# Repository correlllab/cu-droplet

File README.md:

497-6781-1-ND

Droplets: A Swarm Robotics Platform
==========

[Click here to get started!](https://github.com/correlllab/cu-droplet/blob/master/getting_started.md)

The platform has been produced by the Correll Robotics Lab at the University of Colorado Boulder. It is envisioned to be a scalable robotics experimentation environment.

The hardware is comprised of actual robots, and the test bed/floor that experiments are run on. The robots are capable of sensing IR and RGB intensities, actuation using vibration motors, and IR communication. The embedded software layer is what we use to write and compile on-board code for the droplets. Each robot is equipped with an Atmel xmega-128a3u microprocessor capable of running embedded-c.

A simulator has also been developed for this platform. This code has its own repo on <a href="https://github.com/correlllab/cu-droplet-sim">github</a>.

This work is available under a <a href="https://creativecommons.org/licenses/by-nc-sa/4.0/" >Creative Commons Attribution-NonCommercial-ShareAlike License. </a>

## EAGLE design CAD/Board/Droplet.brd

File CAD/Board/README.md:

# README

The files included in this folder are Droplet board schematic files to be used with the EAGLE design program.

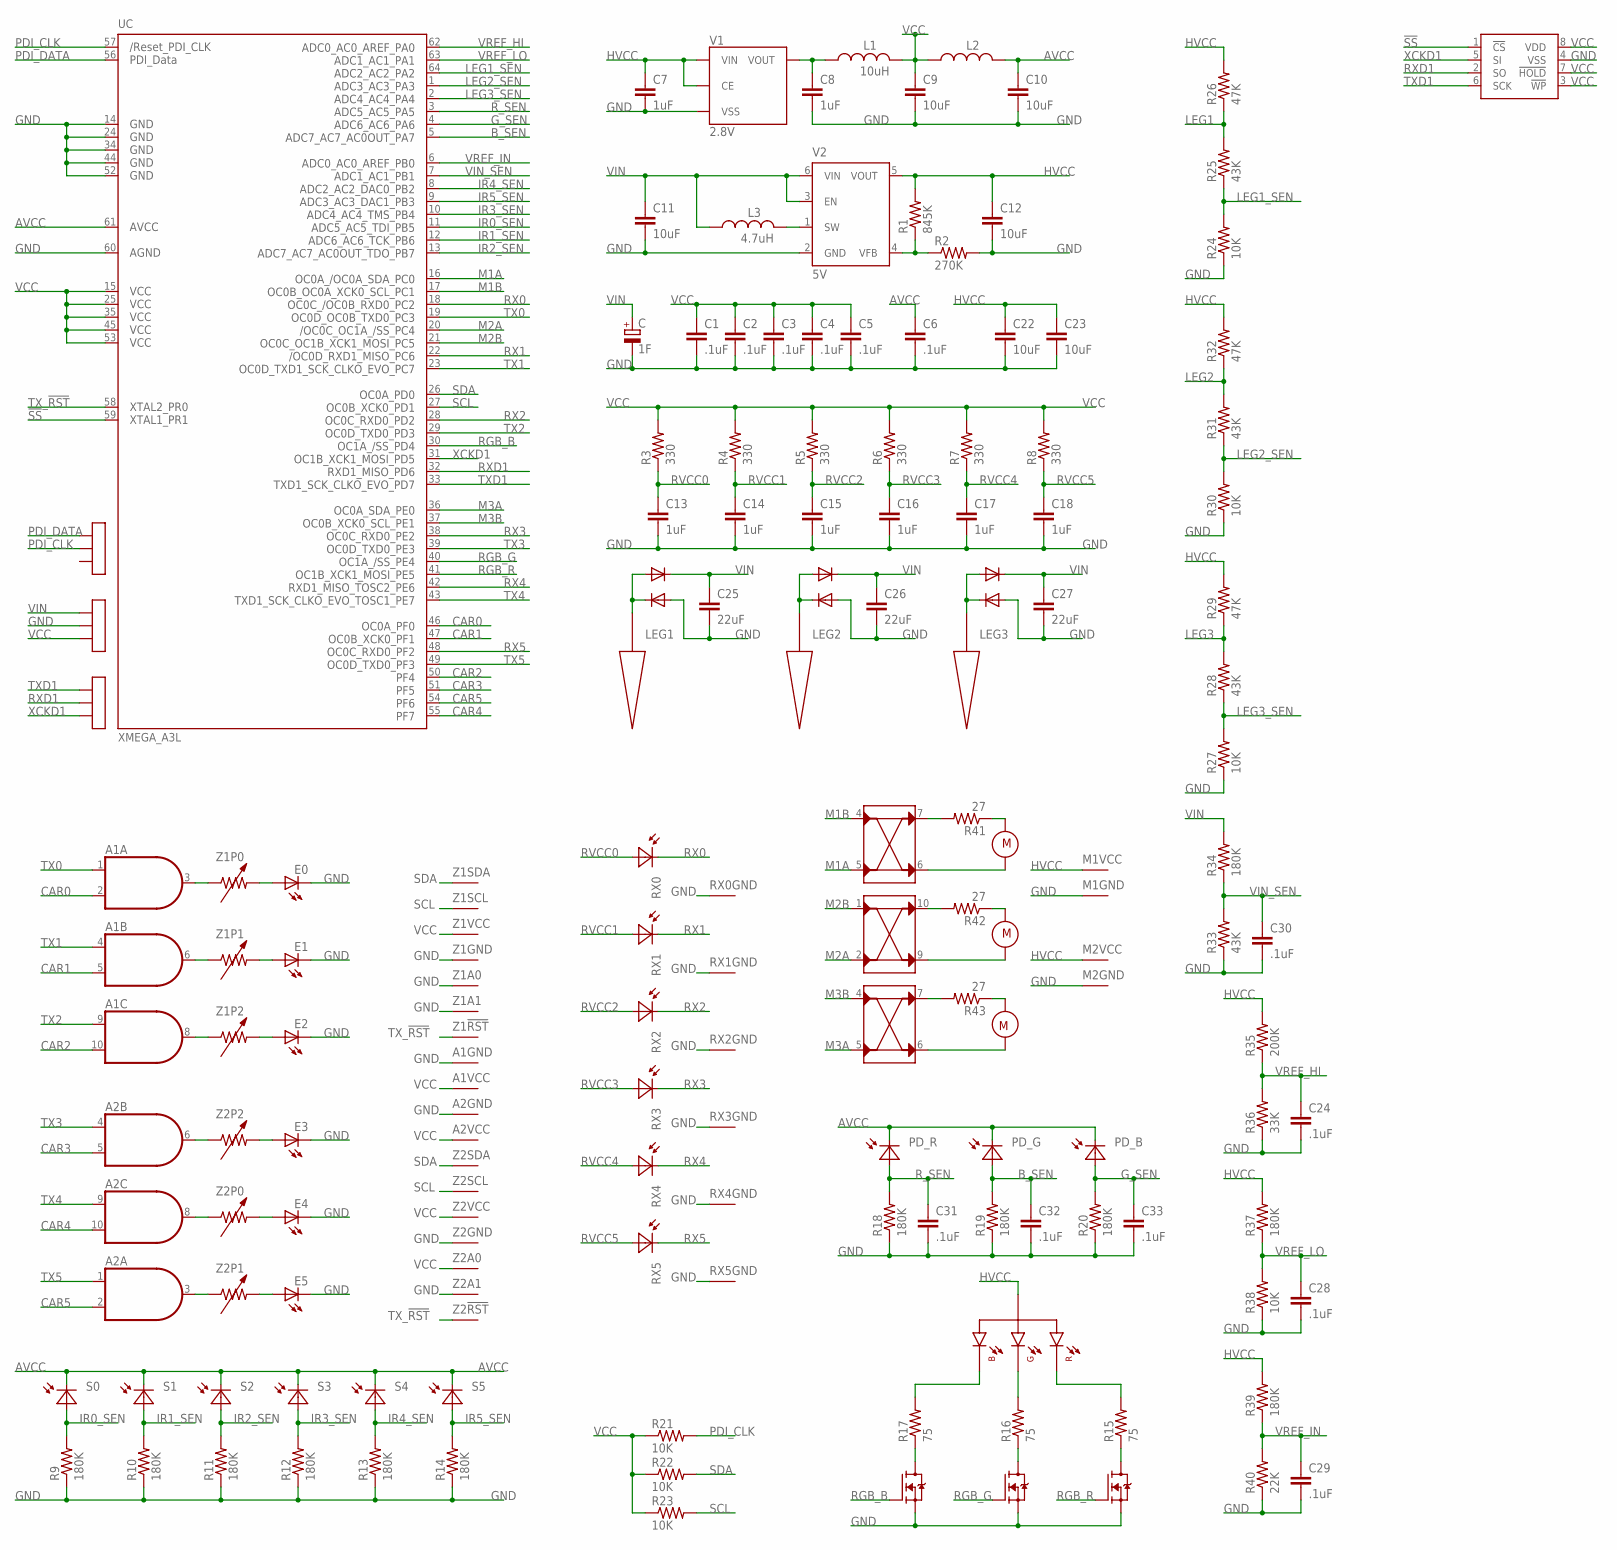
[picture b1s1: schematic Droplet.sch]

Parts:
A1: 7408_X4"; DHVQFN14-L; DIGIKEY 568-2993-1-ND
A2: 7408_X4"; DHVQFN14-L
C: 1F; SUPERCAP
C1, C2, C3, C4, C5, C6, C24, C28, C29, C30, C31, C32, C33: .1uF; 0402
C7, C8, C13, C14, C15, C16, C17, C18: 1uF; 0402
C9, C10, C11, C12, C22, C23: 10uF; 0603
C25, C26, C27: 22uF; 0805
D1, D2, D3, D4, D5, D6: DIODE; SOD-123
E0, E1, E2, E3, E4, E5: IR_LED; 1208-IR
F1, F2: MOSFET-N_X2; SOT-363
L1: 10uH; 0805
L2: INDUCTOR0603; 0603
L3: 4.7uH; 1210
LED: RGB_LED
LEG1, LEG2, LEG3: LEG
M1, M2: HALF-MOTOR_CONTROLLER; DFN-10-EJ
MEM: MRAM; DFN-8
MOT1, MOT2, MOT3: MOTOR; MOTOR_PADS
P1, P2, P3: EDGE_PORT_3; EDGE_CONNECTOR3
PD_B: RGB_PHOTODIODE; RGB_SENSOR
PD_G: RGB_PHOTODIODE; RGB_SENSOR
PD_R: RGB_PHOTODIODE; RGB_SENSOR
R1: 845K; 0402
R2: 270K; 0402
R3, R4, R5, R6, R7, R8: 330; 0402
R9, R10, R11, R12, R13, R14, R18, R19, R20, R34, R37, R39: 180K; 0402
R15, R16, R17: 75; 0402
R21, R22, R23, R24, R27, R30, R38: 10K; 0402
R25, R28, R31, R33: 43K; 0402
R26, R29, R32: 47K; 0402
R35: 200K; 0402
R36: 33K; 0402
R40: 22K; 0402
R41, R42, R43: 27; 0402
RX0, RX1, RX2, RX3, RX4, RX5: IR_RECEIVER
S0, S1, S2, S3, S4, S5: IR_PHOTODIODE; 1208-IR
UC: XMEGA_A3L; MLF-64-L
V1: 2.8V; SOT-25
V2: 5V; SOT-23-6
Z1, Z2: VAR_RESISTOR_X4; QFN-20

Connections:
!SS: MEM.1 (!CS), UC.59 (PR1)
AVCC: C6.1, C10.1, L2.2, PD_B.C1 (C), PD_B.C2 (C), PD_G.C1 (C), PD_G.C2 (C), PD_R.C1 (C), PD_R.C2 (C), S0.C, S1.C, S2.C, S3.C, S4.C, S5.C, UC.61 (AVCC)
B_SEN: C32.1, PD_G.A1 (A), PD_G.A2 (A), R19.2, UC.5 (PA7)
CAR0: A1.2 (I1), UC.46 (PF0)
CAR1: A1.5 (I1), UC.47 (PF1)
CAR2: A1.10 (I1), UC.50 (PF4)
CAR3: A2.5 (I1), UC.51 (PF5)
CAR4: A2.10 (I1), UC.55 (PF7)
CAR5: A2.2 (I1), UC.54 (PF6)
GND: A1.7 (1), A2.7 (1), C.N (-), C1.2, C2.2, C3.2, C4.2, C5.2, C6.2, C7.2, C8.2, C9.2, C10.2, C11.2, C12.2, C13.2, C14.2, C15.2, C16.2, C17.2, C18.2, C22.2, C23.2, C24.2, C25.2, C26.2, C27.2, C28.2, C29.2, C30.2, C31.2, C32.2, C33.2, D2.A, D4.A, D6.A, E0.C, E1.C, E2.C, E3.C, E4.C, E5.C, F1.1 (S), F1.4 (S), F2.1 (S), M1.3 (1), M2.3 (1), MEM.4 (VSS), P2.2A (2), P2.2B (2), R2.2, R9.1, R10.1, R11.1, R12.1, R13.1, R14.1, R18.1, R19.1, R20.1, R24.1, R27.1, R30.1, R33.1, R36.1, R38.1, R40.1, RX0.3 (1), RX1.3 (1), RX2.3 (1), RX3.3 (1), RX4.3 (1), RX5.3 (1), UC.14 (GND1), UC.24 (GND2), UC.34 (GND3), UC.44 (GND4), UC.52 (GND5), UC.60 (AGND), V1.VSS, V2.2 (GND), Z1.2 (1), Z1.5 (1), Z1.14 (1), Z2.5 (1), Z2.14 (1)
G_SEN: C33.1, PD_B.A1 (A), PD_B.A2 (A), R20.2, UC.4 (PA6)
HVCC: C7.1, C12.1, C22.1, C23.1, LED.2 (ANODE), M1.8 (1), M2.8 (1), R1.2, R26.2, R29.2, R32.2, R35.2, R37.2, R39.2, V1.CE, V1.VIN, V2.5 (VOUT)
IR0_SEN: R9.2, S0.A, UC.11 (PB5)
IR1_SEN: R10.2, S1.A, UC.12 (PB6)
IR2_SEN: R11.2, S2.A, UC.13 (PB7)
IR3_SEN: R12.2, S3.A, UC.10 (PB4)
IR4_SEN: R13.2, S4.A, UC.8 (PB2)
IR5_SEN: R14.2, S5.A, UC.9 (PB3)
LEG1: D1.A, D2.C, LEG1.1, R25.2, R26.1
LEG1_SEN: R24.2, R25.1, UC.64 (PA2)
LEG2: D3.A, D4.C, LEG2.1, R31.2, R32.1
LEG2_SEN: R30.2, R31.1, UC.1 (PA3)
LEG3: D5.A, D6.C, LEG3.1, R28.2, R29.1
LEG3_SEN: R27.2, R28.1, UC.2 (PA4)
M1A: M1.5 (IN2), UC.16 (PC0)
M1B: M1.4 (IN1), UC.17 (PC1)
M1Z: M1.6 (OUT2), MOT1.2
M2A: M1.2 (IN2), UC.20 (PC4)
M2B: M1.1 (IN1), UC.21 (PC5)
M2Z: M1.9 (OUT2), MOT2.2
M3A: M2.5 (IN2), UC.36 (PE0)
M3B: M2.4 (IN1), UC.37 (PE1)
M3Z: M2.6 (OUT2), MOT3.1
unnamed: C8.1, L1.1, V1.VOUT
unnamed: R1.1, R2.1, V2.4 (VFB)
unnamed: E0.A, Z1.10 (2)
unnamed: E1.A, Z1.7 (2)
unnamed: E2.A, Z1.17 (2)
unnamed: L3.2, V2.1 (SW)
unnamed: E3.A, Z2.17 (2)
unnamed: E4.A, Z2.10 (2)
unnamed: E5.A, Z2.7 (2)
unnamed: A1.3 (O), Z1.9 (1)
unnamed: A1.6 (O), Z1.8 (1)
unnamed: A1.8 (O), Z1.18 (1)
unnamed: A2.6 (O), Z2.18 (1)
unnamed: A2.8 (O), Z2.9 (1)
unnamed: A2.3 (O), Z2.8 (1)
unnamed: F1.6 (D), R17.1
unnamed: F1.3 (D), R16.1
unnamed: F2.6 (D), R15.1
unnamed: LED.3 (B), R17.2
unnamed: LED.4 (G), R16.2
unnamed: M1.7 (OUT1), R41.2
unnamed: MOT1.1, R41.1
unnamed: M1.10 (OUT1), R42.2
unnamed: MOT2.1, R42.1
unnamed: LED.1 (R), R15.2
unnamed: M2.7 (OUT1), R43.2
unnamed: MOT3.2, R43.1
PDI_CLK: P1.2A (2), P1.2B (2), R21.2, UC.57 (RESET)
PDI_DATA: P1.1A (1), P1.1B (1), UC.56 (PDI_DATA)
RGB_B: F1.2 (G), UC.30 (PD4)
RGB_G: F1.5 (G), UC.40 (PE4)
RGB_R: F2.2 (G), UC.41 (PE5)
RVCC0: C13.1, R3.1, RX0.2 (A)
RVCC1: C14.1, R4.1, RX1.2 (A)
RVCC2: C15.1, R5.1, RX2.2 (A)
RVCC3: C16.1, R6.1, RX3.2 (A)
RVCC4: C17.1, R7.1, RX4.2 (A)
RVCC5: C18.1, R8.1, RX5.2 (A)
RX0: RX0.1 (C), UC.18 (PC2)
RX1: RX1.1 (C), UC.22 (PC6)
RX2: RX2.1 (C), UC.28 (PD2)
RX3: RX3.1 (C), UC.38 (PE2)
RX4: RX4.1 (C), UC.42 (PE6)
RX5: RX5.1 (C), UC.48 (PF2)
RXD1: MEM.2 (SO), P3.2A (2), P3.2B (2), UC.32 (PD6)
R_SEN: C31.1, PD_R.A1 (A), PD_R.A2 (A), R18.2, UC.3 (PA5)
SCL: R23.2, UC.27 (PD1), Z1.3 (1), Z2.3 (1)
SDA: R22.2, UC.26 (PD0), Z1.4 (1), Z2.4 (1)
TX0: A1.1 (I0), UC.19 (PC3)
TX1: A1.4 (I0), UC.23 (PC7)
TX2: A1.9 (I0), UC.29 (PD3)
TX3: A2.4 (I0), UC.39 (PE3)
TX4: A2.9 (I0), UC.43 (PE7)
TX5: A2.1 (I0), UC.49 (PF3)
TXD1: MEM.6 (SCK), P3.1A (1), P3.1B (1), UC.33 (PD7)
TX_!RST: UC.58 (PR0), Z1.13 (1), Z2.13 (1)
VCC: A1.14 (1), A2.14 (1), C1.1, C2.1, C3.1, C4.1, C5.1, C9.1, L1.2, L2.1, MEM.3 (!WP), MEM.7 (!HOLD), MEM.8 (VDD), P2.3A (3), P2.3B (3), R3.2, R4.2, R5.2, R6.2, R7.2, R8.2, R21.1, R22.1, R23.1, UC.15 (VCC1), UC.25 (VCC2), UC.35 (VCC3), UC.45 (VCC4), UC.53 (VCC5), Z1.15 (1), Z2.2 (1), Z2.15 (1)
VIN: C.P (+), C11.1, C25.1, C26.1, C27.1, D1.C, D3.C, D5.C, L3.1, P2.1A (1), P2.1B (1), R34.2, V2.3 (EN), V2.6 (VIN)
VIN_SEN: C30.1, R33.2, R34.1, UC.7 (PB1)
VREF_HI: C24.1, R35.1, R36.2, UC.62 (PA0)
VREF_IN: C29.1, R39.1, R40.2, UC.6 (PB0)
VREF_LO: C28.1, R37.1, R38.2, UC.63 (PA1)
XCKD1: MEM.5 (SI), P3.3A (3), P3.3B (3), UC.31 (PD5)

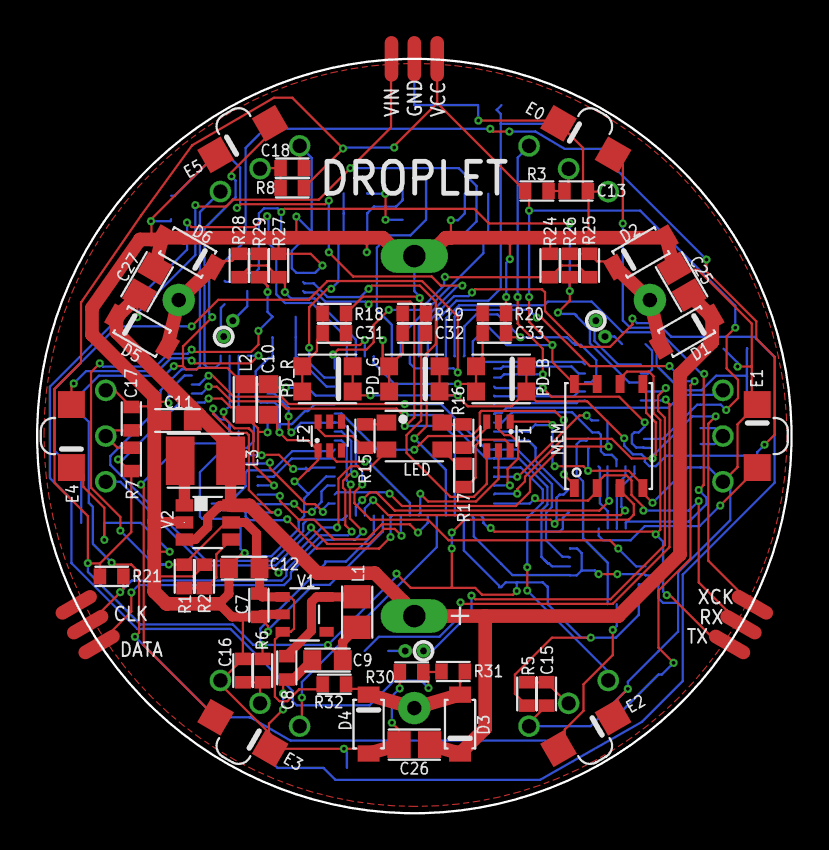
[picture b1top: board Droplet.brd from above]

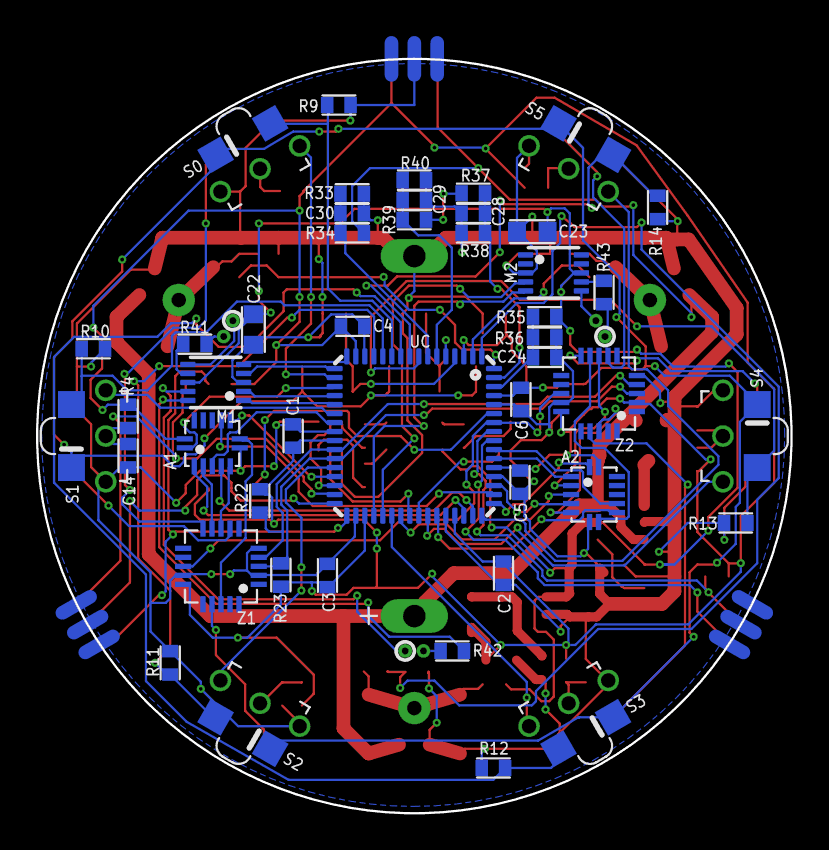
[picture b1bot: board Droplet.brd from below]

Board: 2 copper layers, 41.9 x 41.9 mm, 126 parts (56 on the bottom side), 96 nets.

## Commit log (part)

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2016-07-02 A runnin version of distributed camouflage algorithm
2016-07-03 Modify for the non-audio droplets, and calibrate the rgb sensors. The baselines were reset to 0 which I don't think is right, so I comment those lines.
2016-07-04 Need to modify according the notes
2016-07-06 Add print functions to print information needed afterwards
2016-07-06 Nothing special
2016-07-06 add calibration for RGB with white light
2016-07-07 Modify to add calibreation by wrting the dark readings to EEPROM. By John Klingner
2016-07-07 A working one, don't want to change the logic again.
2016-07-08 V-0.9
2016-07-10 Eulerian Distance for colors seems no better
2016-07-12 small change on pattern descriptors?
2016-07-16 Version with 3 patterns, doesnt work well on the droplet, mainly the pattern fomation phase. I think that might be the wrong reflection setting?
2016-07-19 Updating master with minor updates to things from ping_pong branch. Mostly, these are improvements to the Waiting for TWI error printout.
2016-07-19 Finally added all the files needed to order your own Droplet Circuit Boards
2016-07-19 Recommenting after pulling from master.
2016-08-04 Updated the API document to include additional information about serial commands, printf, and size-explicit variable types.
2016-09-16 Code that was (almost) used for ICRA.
2016-09-22 Made good progress implementing particle filter, though there are a lot of comments so far.
2016-09-29 Particle filter working pretty well for two droplets, though it's slow to converge.
2016-09-29 Changes updated
2016-09-30 Updated range_model for improve RNB performance.
2016-10-11 ..Accidentally did a ton of refactoring. Took all variables and functions which only needed local scope and moved them to the C file and made them static. Also modified the scheduler to go back to ju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
2016-10-12 Major bugs worked out of the batch particle updates. Trouble with batch approach is that trying to do all the computation all at once means the computation takes longer than a frame. About twice as l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
2016-10-13 Made some good progress cleaning things up from yesterday's big changes. Switched to x,y,o difference tracking instead of r,b,h, but kept it so that it's easy to switch from one to the other. x,y,o i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
2016-10-15 Particle filter seems to be working well/correctly for jsut two robots. Some more subtle issues with multiple robots. I think it's now working roughly as well as it did before I lumped everything tog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
2016-10-25 I've weeded out all of the bugs I can with particle filter stuff. If important bugs remain, they're subtle. Overall results are still not great. I'm going to collect all of the data from some droplet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
2016-10-27 This code is for collecting and printing all the data a droplet has to consider for figuring out its position.
2016-10-27 Trying to set things back how they were before I tore out all the particle filter stuff.
2016-10-29 End of week commit. Still working on adding don't-conflict-with-source logic to particle filter.
2016-10-31 Some more changes from my working branch. did some more work on the collisions checking - it now requires pre-calibration.
2016-11-02 Made some good progress on bugs in the camouflage code.
2016-11-05 Yang: adding corner reflection as suggested by John in function changeColor
2016-11-15 Small fixes to user_template.c
2016-11-23 Going away for Thanksgiving commit.
2016-11-30 Master in good shape again.
2016-12-01 Tests working pretty well.
2016-12-02 Added reference PDF for Audio Droplets
2016-12-14 Working.. okay? Worked in small test. Struggling with larger test.
2016-12-16 Few changes needed to be made for compilability.
2016-12-29 Made some improvements to the code; it actually seems to be working fairly well in tests of around a dozen droplets.
2017-01-14 Finished updating with 80% more Kalman approach. Early indications are that it works like magic. Will do full-scale tests, next.
2017-01-19 Full kalman mostly implemented.
2017-01-26 Trying a tweak to how this works.
2017-01-26 Made some forthere tweaks. Going to turn back on the full r,b,h capabilities of range and bearing.
2017-01-30 Need to switch branches.
2017-02-03 Finished re-fixing range and bearing (now with heading reincluded). That, on top of the Covariance Interference algorithm, seems to be working very well indeed. Tentatively best I've seen; still need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
2017-02-08 continued progress! multi-filter implemented with optimal (I think) fusing of the multiple filters.
2017-02-08 Accidentally left one thing in user_template.c, needed to clean it out.
2017-02-08 Moved the pong-specific stuff out of positions.c and in to pong.c
2017-02-14 Further improvements!
2017-02-23 Haven't been able to make much progress due to multiprogrammer failure, but I want to switch branches.
2017-02-28 Added functions to read other droplets' motor_adjust values and
    chec if a droplet is calibrated or not.
2017-03-02 More changes to motor_adjust_values passing
2017-03-05 printing read_motor_settings after storing in an array
2017-03-17 edge following implemented without using range and bearing- works only for close distances
2017-03-21 Updated send_motor_settings
2017-03-22 This didn't get fixed right when moving code to master.
2017-03-22 Fixed the weird little issue.
2017-03-23 Finished stripping out the four-filters-at-once stuff.
2017-04-01 Back down to single filter, but I left all the pieces for multi-filter approach commented out in case I feel the need to go back, again. Made progress on implementing Covariance Union approach, which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
2017-04-03 Pulled in TC_ fixes from master.
2017-04-03 A few more little changes for Master. The randomly-big-vibrations-at-beginning-of-motion bug is finally fixed! (Thanks, Praveen, for helping identify that. Also an attempt to improve the task_list_cl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
2017-04-12 Greatly cleaned up the architecture of global localization; no persistent data structure required. Also implemented a quick-and-dirty CSMA-lite for communicating measurements to other Droplets.
2017-04-12 Successfully restructed the localization code in to a fairly isolated package.
2017-04-12 Minor reordernig of functions in localization.c
2017-04-14 Preparing to push to master.
2017-04-19 Need to commit for test.
2017-04-20 need to implement getOtherPos() and datastructure
2017-04-24 Trying to figure out this weird bug.
2017-04-26 Major refactoring of h file include hierarchy.
2017-04-27 Making progress on actually implementing pong on top of the localization code.
2017-05-30 Made a number of small changes throughout to accomadate for custom makefile switchover. Should just be refactoring-type stuff.
2017-05-30 Somehow I must have accidentally deleted my .gitignore and .gitattributes files in this branch. So I've unfixed that, and updated .gitignore to ignore the compiler output files generated during compi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
2017-05-30 Handling custom makefile update.
2017-05-31 Bare minimum localization bug test suite.
2017-05-31 I've made several local changes to fix the bug, but without any luck. Going to set this to be an exact copy of origin master and redo changes from there, maybe.
2017-05-31 Removing *.hex files from .gitignore (temporarily?)
2017-05-31 Just updated makefile to project name.
2017-05-31 sp_driver issue persists.
2017-06-01 Hacky fix for localization bug implemented, pending a proper fix.
2017-06-01 Rename getting_started.md to getting_started_old.md
2017-06-01 Started working on grid initialization
2017-06-02 Grid initialization finished
2017-06-06 Bug fixed; set_all_ir_powers can now be used as normal.
2017-06-08 Making progress getting ball bouncing up and running again with localization.
2017-06-16 Initial commit.
2017-06-20 Minor folder reorganization, and added a few independent study reports.
2017-07-06 follow bot kinda working.
2017-07-12 Added grid_init algo and game_of_life program
2017-07-31 Switching to working on communication data, now.
2017-08-01 Working pretty well. I switched things over to a CSMA approach for both ping and ack and it made a huge difference.
2017-08-04 Need to test something.
2017-08-04 grid version without localization, about to use localization
2017-08-04 add compile setup file
2017-08-05 Removed Conf value in the range and bearing message
2017-08-05 Aug_5_run_1 version, works well
2017-08-09 Definitely still a work in progress.
2017-08-09 patternNode list
2017-08-10 Continued progress. sendBotPosMsg and associated functions implemented.
2017-08-10 For mottle pattern, threshold=50, factor=0.55
2017-08-11 makes turing_color 'on' for black, 'off' for white
2017-08-15 Added CSMA template and GoL using CSMA
2017-08-17 reviewed, start testing
2017-08-18 add print functions
2017-08-24 modified the way to store activator and inhibitor for pattern formation; needs to fix the definiction of activator and inhibitor orientation
2017-08-26 Added NelderMead algorithm to find optimal pattern angle and stripe width.
2017-08-30 test nelder-mead method
2017-09-01 Minor changes to printfs.
2017-09-06 I've made a few changes?
2017-09-12 Nothing significant.
2017-09-25 Fixed known bug. Working now?
2017-09-26 Working great, now. Going to pull in to master.
2017-09-26 Removing one commented line which will now never be uncommented.
2017-09-26 Missed a spot on the road to camel case
2017-10-03 before merging
2017-10-06 Removed an unused byte from the message header, reducing the header size to 7 bytes. Also made some improvements to ff_sync.
2017-10-25 removed merge conflicts
2018-01-03 Added an experimental feature: Droplet will move a bit if its capacitor is low on power, in an attempt to find a good patch of floor.
2018-01-23 Making progress.
2018-01-29 Merging in fixes for broken comunication code discovered in master.
2018-02-07 About to change the keyboard size; want to save this.
2018-02-09 Got all of the pieces of the keyboard written. Still need to debug, and test. Most likely source of bugs is a linked list implementation to store recently-seen events.
2018-02-19 Only read flash done
2018-02-19 Removed doc
2018-02-20 Need to temporarily switch branches.
2018-02-22 Removed hardcoded address
2018-02-22 Power code changes merged.\r\n
2018-02-24 Refactored 'keyboard.h' and 'keypress_queue.*' to be more generic: 'button.h' and 'button_press_queue.*'. Added the two Mouse roles to the Button enumerator (formerly KeyboardKey enumerator).
2018-02-27 Changing branches again.
2018-03-01 Self programming working with hex from python
2018-03-02 First attempt at complete Mouse and Keyboard code. Not thoroughly tested yet; almost certainly some bugs.
2018-03-06 Adding build folder
2018-03-14 arbitrary code - step 2 done
2018-03-15 Keyboard still working pretty well. Mouse still has issues.
2018-03-20 Did some relatively minor refactoring of the code in the hopes that better time management will improve the keyboard communications.
2018-03-21 Brought in a bunch of changes I made in MouseKeyboard branch. Includes a refactored method for accessing RnB data, and updated documentation.
2018-03-24 Multiple lines self programming - bug solved
2018-03-26 Forgot to 'git add' the files before the previous commit.
2018-03-26 Added the mouseKeyboard code to the droplet_programs folder.
2018-03-31 Added a few functions for Riya to use.
2018-04-10 random back-off at beginning of message slot
2018-04-24 befor integration
2018-04-25 Selfprogram and linker script changes done, problem
2018-05-09 updated mic.c
2018-05-18 Set up for now.
2018-05-31 Done for now.
2018-05-31 Cleaning things up.
2018-05-31 Decided I should put this back.
2018-06-02 Continued cleaning up. Made substantial changes to the python script which mean that the pipeline is broken until the python script has had coded added to send all relevant data, and the droplets cod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
2018-06-02 Tried to add enough to the C code and Python code that the reprogramming messages were at least being sent for testing purposes, but there seem to still be some bugs.
2018-06-05 Cleaning out some unused portions of the code, specifically: flash_api and sp_driver. What functionality these once provided is no longer needed or has been replaced with the eeprom driver.
2018-07-06 Updated ir_comm.h
2018-07-12 made changes to rtc ISR for ffsync
2018-07-26 Update ir_comm.c
    Empirical data-driven rescaling of the 'delay' measured for the timed cmd functions (receivedRnbCmd & receivedIrSyncCmd), since there seems to be a linear error in the delay when measured this way.
2018-08-23 Updated for changes in master.
2018-08-23 Updated for CSMA.
2018-10-26 Code draft, ie. implementations of nec_ir, complete. Now testing.
2018-10-27 Working, but localization isn't great with only one seed Droplet.
